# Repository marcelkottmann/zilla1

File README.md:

# zilla1
an arduino controlled analog synthesizer

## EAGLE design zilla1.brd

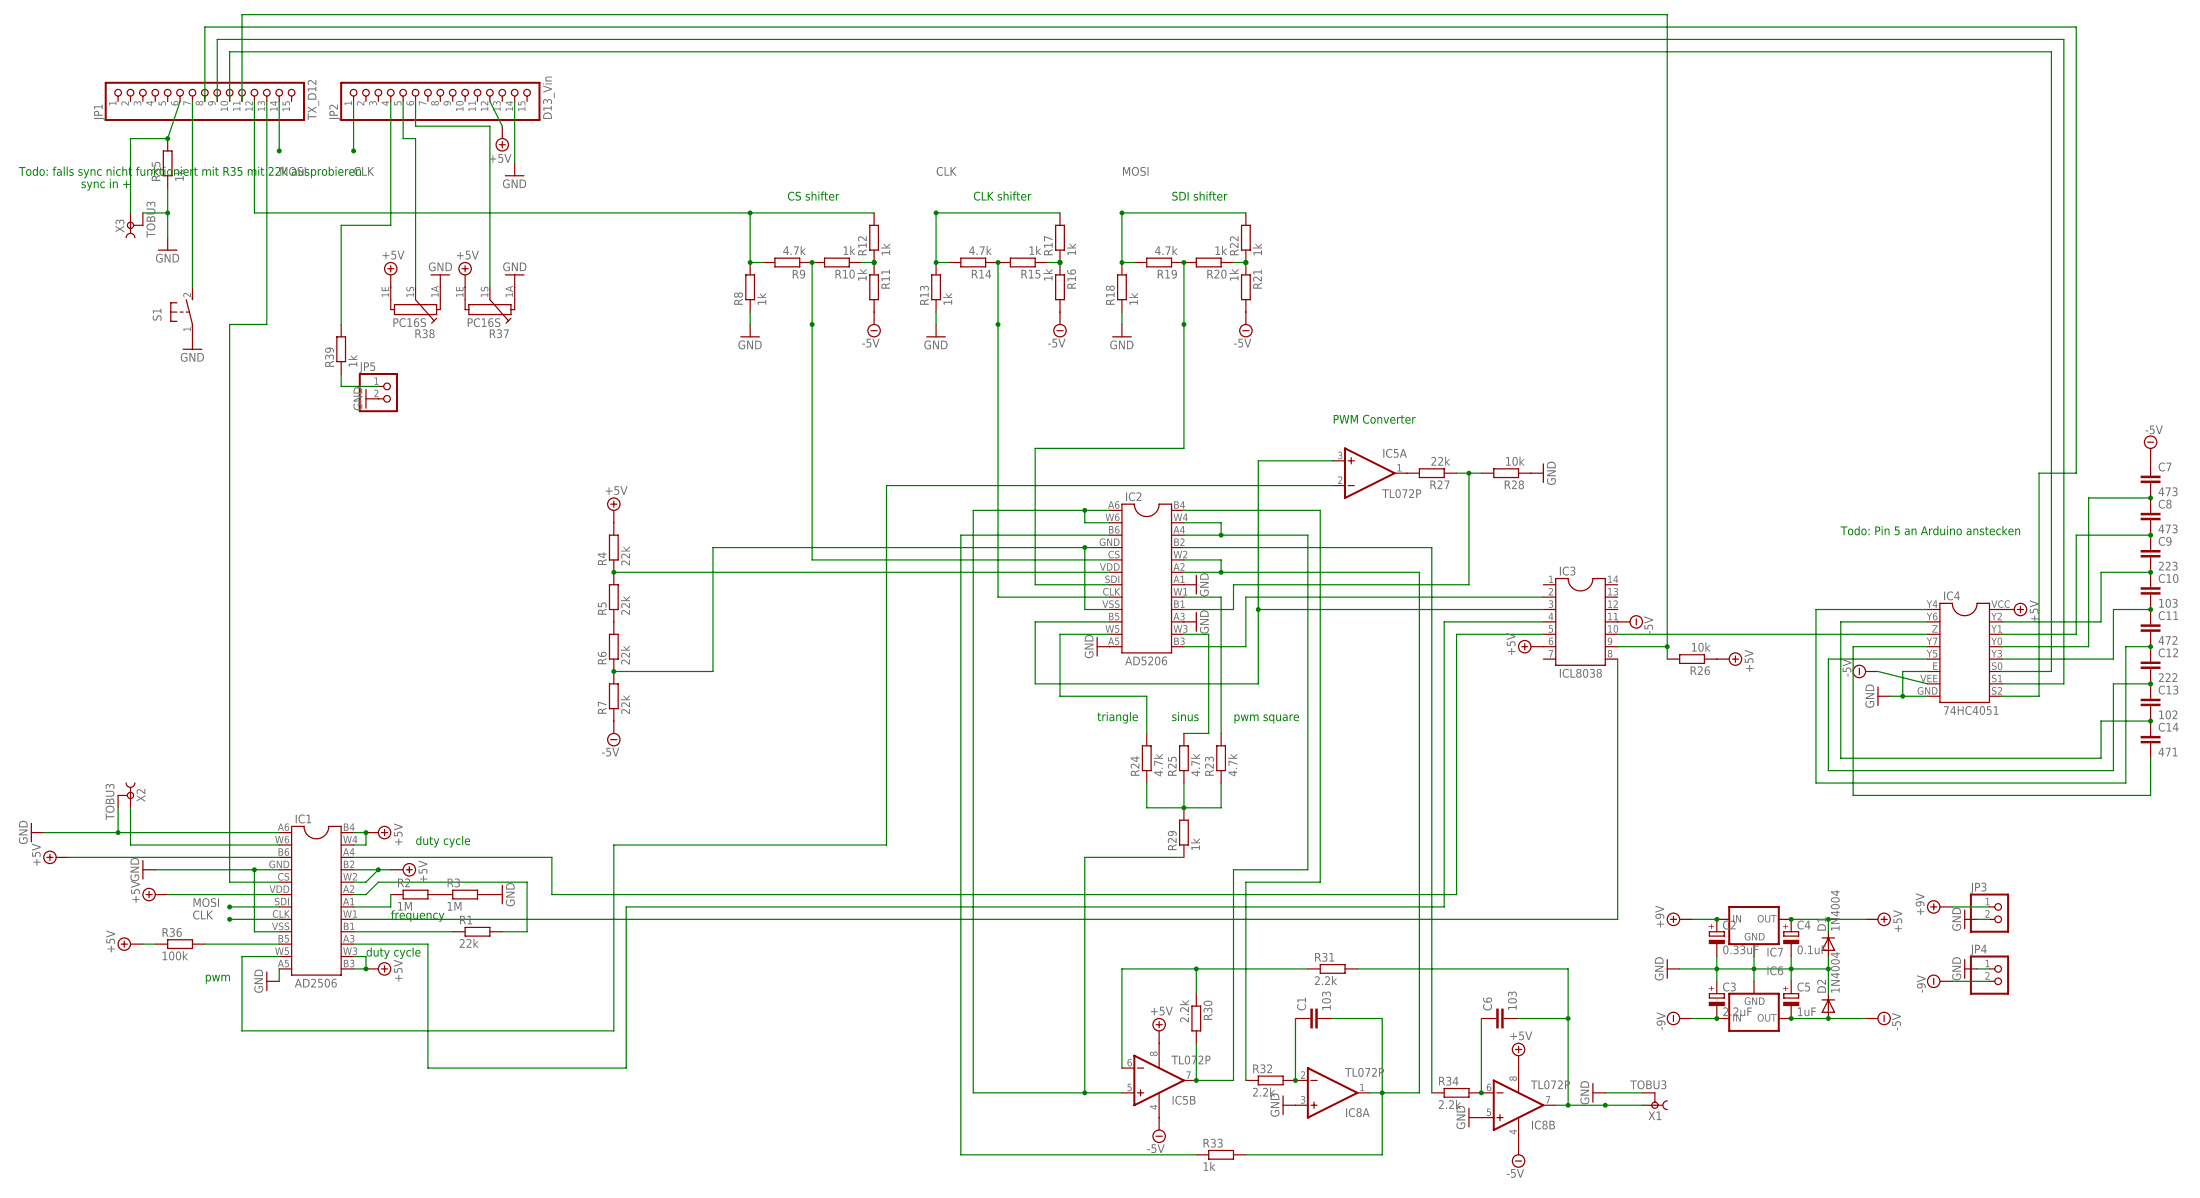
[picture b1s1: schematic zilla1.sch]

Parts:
C1, C6, C10: 103; C025-024X044
C2: 0.33uF; E2-5
C3: 2.2uF; E2-5
C4: 0.1uF; E2-5
C5: 1uF; E2-5
C7, C8: 473; C025-024X044
C9: 223; C025-024X044
C11: 472; C025-024X044
C12: 222; C025-024X044
C13: 102; C025-024X044
C14: 471; C025-024X044
D1, D2: 1N4004; DO41-10
IC1: AD2506; AD5206
IC2: AD5206
IC3: ICL8038; DIL14
IC4: 74HC4051; DIL16
IC5, IC8: TL072P; DIL08
IC6: 79XXS
IC7: 78XXS
JP1: TX_D12; 1X15
JP2: D13_Vin; 1X15
JP3, JP4, JP5: PINHD-1X2; 1X02
R1, R4, R5, R6, R7, R27: 22k; 0207/7
R2, R3: 1M; 0207/7
R8, R10, R11, R12, R13, R15, R16, R17, R18, R20, R21, R22, R29, R33, R35, R39: 1k; 0207/7
R9, R14, R19, R23, R24, R25: 4.7k; 0207/7
R26, R28: 10k; 0207/7
R30, R31, R32, R34: 2.2k; 0207/7
R36: 100k; 0207/7
R37, R38: PC16S
S1: 31-XX; B3F-31XX
X1, X2, X3: TOBU3

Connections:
+5V: C4.+, D1.C, IC1.B2 (21), IC1.B3 (13), IC1.B4 (24), IC1.B6 (3), IC1.VDD (6), IC1.W2 (20), IC1.W3 (14), IC1.W4 (23), IC3.6, IC4.VCC (16), IC5.8 (V+), IC7.OUT, IC8.8 (V+), JP2.12, R4.2, R26.1, R36.1, R37.1E, R38.1E
+9V: C2.+, IC7.IN, JP3.1
-5V: C5.-, C7.1, D2.A, IC3.11, IC4.VEE (7), IC5.4 (V-), IC6.OUT, IC8.4 (V-), R7.1, R11.2, R16.2, R21.2
-9V: C3.-, IC6.IN, JP4.2
CLK: IC1.CLK (8), JP2.1, R13.2, R14.2, R17.2
GND: C2.-, C3.+, C4.-, C5.+, D1.A, D2.C, IC1.A5 (12), IC1.A6 (TEST), IC1.GND (4), IC1.VSS (9), IC2.A1 (18), IC2.A3 (15), IC2.A5 (12), IC4.E (6), IC4.GND (8), IC6.GND, IC7.GND, IC8.3 (+IN), IC8.5 (+IN), JP2.14, JP3.2, JP4.1, JP5.2, R3.2, R8.1, R13.1, R18.1, R28.1, R35.1, R37.1A, R38.1A, S1.1, X1.2, X1.2@1 (2), X1.2@2 (2), X2.2, X2.2@1 (2), X2.2@2 (2), X3.2, X3.2@1 (2), X3.2@2 (2)
MOSI: IC1.SDI (7), JP1.14, R18.2, R19.2, R22.2
unnamed: IC1.B1 (16), R1.1
unnamed: R2.2, R3.1
unnamed: IC1.A1 (18), R2.1
unnamed: IC1.W1 (17), IC3.8
unnamed: IC2.VDD (6), R4.1, R5.2
unnamed: R5.1, R6.2
unnamed: IC2.GND (4), IC2.VSS (9), R6.1, R7.2
unnamed: JP1.12, R8.2, R9.2, R12.2
unnamed: IC2.CS (5), R9.1, R10.2
unnamed: R10.1, R11.1, R12.1
unnamed: IC1.CS (5), JP1.13
unnamed: IC2.B3 (13), IC3.2
unnamed: IC2.CLK (8), R14.1, R15.2
unnamed: R15.1, R16.1, R17.1
unnamed: IC2.B5 (10), IC3.3, IC5.3 (+IN)
unnamed: IC2.SDI (7), R19.1, R20.2
unnamed: R20.1, R21.1, R22.1
unnamed: IC2.W3 (14), R25.2
unnamed: IC2.W5 (11), R24.2
unnamed: IC3.9, JP1.11, R26.2
unnamed: IC2.W1 (17), R23.2
unnamed: R23.1, R24.1, R25.1, R29.2
unnamed: IC5.1 (OUT), R27.2
unnamed: IC2.B1 (16), R27.1, R28.2
unnamed: IC3.10, IC4.Z (3)
unnamed: IC2.A6 (TEST), IC2.W6 (VCC), IC5.5 (+IN), R29.1
unnamed: IC4.S0 (11), JP1.10
unnamed: IC4.S1 (10), JP1.9
unnamed: IC2.A4 (22), IC2.W4 (23), IC5.7 (OUT), R30.2
unnamed: IC5.6 (-IN), R30.1, R31.1
unnamed: C6.1, IC8.6 (-IN), R34.2
unnamed: C1.1, IC8.2 (-IN), R32.2
unnamed: C1.2, IC2.A2 (19), IC2.W2 (20), IC8.1 (OUT), R33.2
unnamed: C7.2, C8.1, IC4.Y0 (13)
unnamed: C6.2, IC8.7 (OUT), R31.2, X1.1
unnamed: IC2.B4 (24), R32.1
unnamed: IC2.B2 (21), R34.1
unnamed: IC2.B6 (3), R33.1
unnamed: IC1.W5 (11), IC5.2 (-IN)
unnamed: IC1.B5 (10), R36.2
unnamed: C8.2, C9.1, IC4.Y1 (14)
unnamed: C9.2, C10.1, IC4.Y2 (15)
unnamed: C10.2, C11.1, IC4.Y3 (12)
unnamed: C11.2, C12.1, IC4.Y4 (1)
unnamed: C12.2, C13.1, IC4.Y5 (5)
unnamed: C13.2, C14.1, IC4.Y6 (2)
unnamed: IC4.S2 (9), JP1.8
unnamed: IC1.A3 (15), IC3.4
unnamed: IC1.A4 (22), IC3.5
unnamed: JP1.6, R35.2, X3.1
unnamed: JP2.5, R38.1S
unnamed: C14.2, IC4.Y7 (4)
unnamed: JP2.6, R37.1S
unnamed: IC1.A2 (19), R1.2
unnamed: IC1.W6 (VCC), X2.1
unnamed: JP1.7, S1.2 (S)
unnamed: JP2.4, R39.2
unnamed: JP5.1, R39.1

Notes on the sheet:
CS shifter
CLK shifter
SDI shifter
PWM Converter
pwm square
triangle
sinus
Todo: Pin 5 an Arduino anstecken
duty cycle
frequency
pwm
sync in +
Todo: falls sync nicht funktioniert mit R35 mit 22k ausprobieren

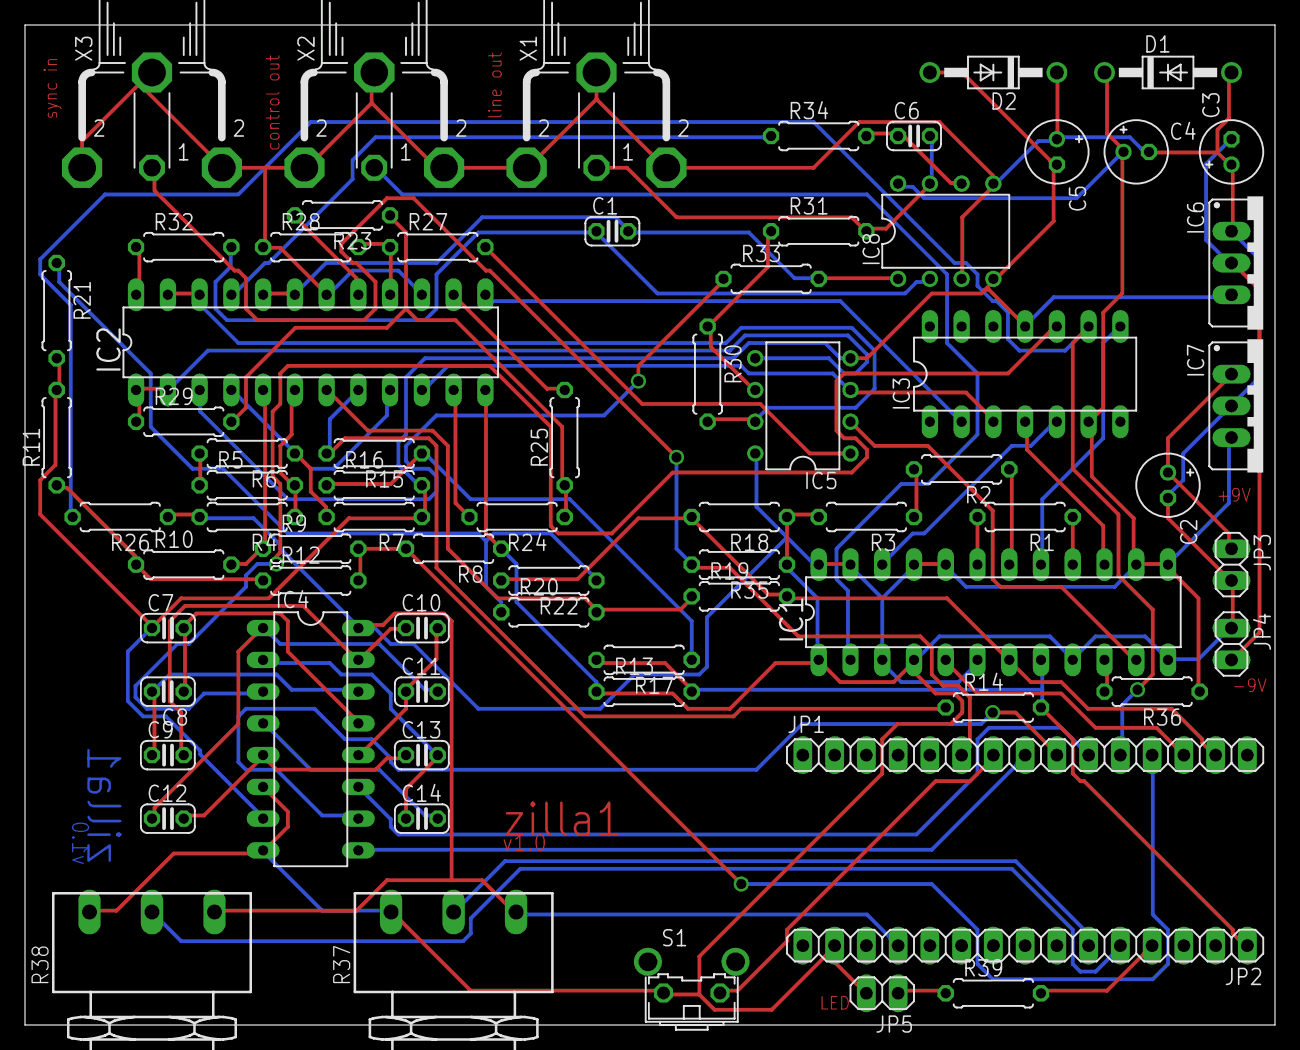
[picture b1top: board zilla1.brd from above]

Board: 2 copper layers, 100.0 x 80.0 mm, 72 parts (0 on the bottom side), 65 nets.

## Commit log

2015-08-27 initial cmmit of eagle files
